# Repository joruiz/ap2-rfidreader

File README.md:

ap2-rfidreader
==============

Rfid Reader module for the Agile Prototyping Plaltform

Based on SonMicro SM125-IC RFID reader. More information in http://www.sonmicro.com/en/index.php?option=com_content&view=article&id=48&Itemid=64

Libraries:
 - For Arduino, use https://github.com/joruiz/SM125

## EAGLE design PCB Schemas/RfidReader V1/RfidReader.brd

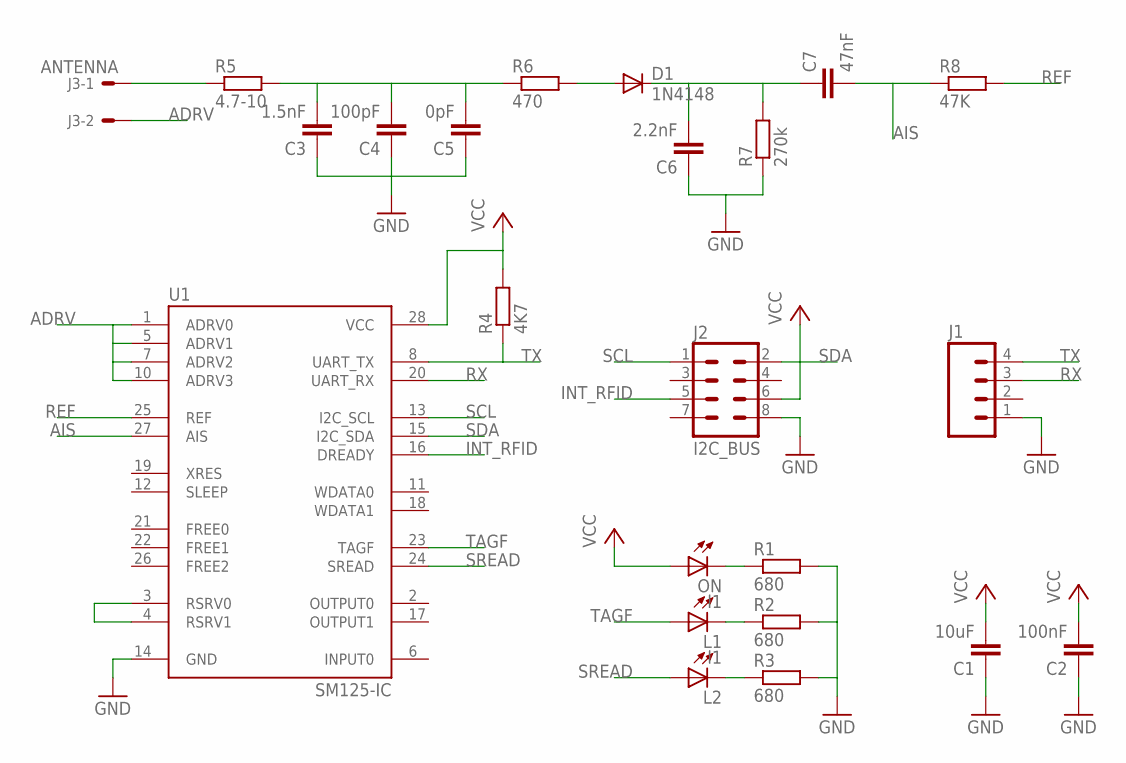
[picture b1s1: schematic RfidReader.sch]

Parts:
C1: 10uF; C0805
C2: 100nF; C0805
C3: 1.5nF; C0805
C4: 100pF; C0805
C5: 0pF; C0805
C6: 2.2nF; C0805
C7: 47nF; C0805
D1: 1N4148; D0805
J1: M04PTH; 1X04
J2: I2C_BUS; SOCKET04X2_ANGLE
J3: ANTENNA; 7395-02
L1: l1; CHIPLED_0805
L2: LEDCHIPLED_0805; CHIPLED_0805
ON: l1; CHIPLED_0805
R1, R2, R3: 680; M0805
R4: 4K7; M0805
R5: 4.7-10; M0805
R6: 470; M0805
R7: 270k; M0805
R8: 47K; M0805
U1: SM125-IC; SOIC28

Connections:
ADRV: J3.2, U1.1 (ADRV0), U1.5 (ADRV1), U1.7 (ADRV2), U1.10 (ADRV3)
AIS: C7.2, R8.1, U1.27 (AIS)
GND: C1.1, C2.1, C3.1, C4.1, C5.1, C6.1, J1.1, J2.8, R1.2, R2.2, R3.2, R7.1, U1.14 (GND)
INT_RFID: J2.5, U1.16 (DREADY)
unnamed: C3.2, C4.2, C5.2, R5.2, R6.1
unnamed: C6.2, C7.1, D1.C, R7.2
unnamed: D1.A, R6.2
unnamed: U1.3 (RSRV0), U1.4 (RSRV1)
unnamed: J3.1, R5.1
unnamed: ON.C, R1.1
unnamed: L1.C, R2.1
unnamed: L2.C, R3.1
REF: R8.2, U1.25 (REF)
RX: J1.3, U1.20 (UART_RX)
SCL: J2.1, U1.13 (I2C_SCL)
SDA: J2.2, U1.15 (I2C_SDA)
SREAD: L2.A, U1.24 (SREAD)
TAGF: L1.A, U1.23 (TAGF)
TX: J1.4, R4.1, U1.8 (UART_TX)
VCC: C1.2, C2.2, J2.6, ON.A, R4.2, U1.28 (VCC)

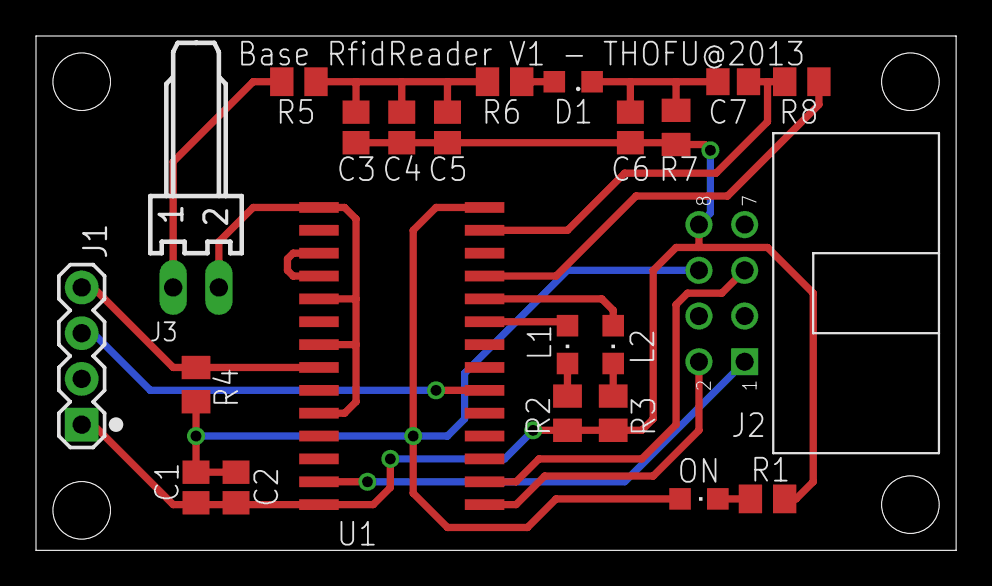
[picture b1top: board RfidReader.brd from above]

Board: 2 copper layers, 51.1 x 28.6 mm, 23 parts (0 on the bottom side), 20 nets.

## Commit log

2014-06-05 Added schematic and board for RfidReader peripheral

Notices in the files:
parts and their libraries:
SparkFun-Connectors: Licensing: CC v3.0 Share-Alike You are welcome to use this library for commercial purposes.
